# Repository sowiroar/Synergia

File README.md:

# Céfiro
Céfiro is an air quality monitoring project that integrates environmental sensors, embedded systems and machine learning models to predict and analyze atmospheric conditions in the city of Manizales. The project collects data on variables such as temperature, humidity, CO2 concentration and air quality to generate reports and visualizations on the environmental status in real time and over time.

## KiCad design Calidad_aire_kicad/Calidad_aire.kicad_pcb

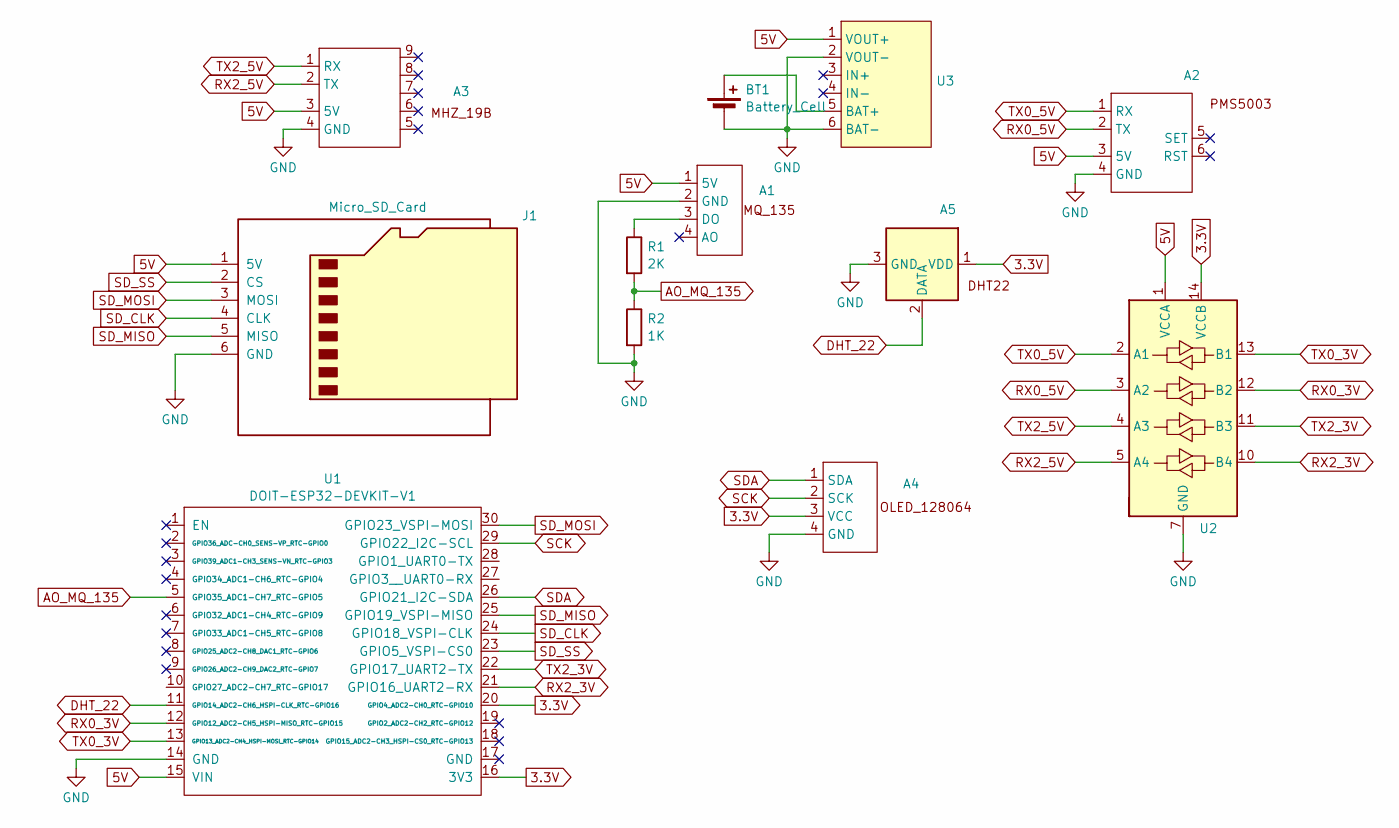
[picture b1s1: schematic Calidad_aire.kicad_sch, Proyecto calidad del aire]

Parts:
A1: MQ_135
A2: TerminalBlock_bornier-4_P5.08mm
A3: MH_Z19B
A4: OLED_128064
A5: DHT22
BT1: Battery_Cell; TerminalBlock_bornier-2_P5.08mm
J1: Micro_SD_Card; microSD
R1: 2K; R_Axial_DIN0414_L11.9mm_D4.5mm_P15.24mm_Horizontal
R2: 1K; R_Axial_DIN0414_L11.9mm_D4.5mm_P15.24mm_Horizontal
U1: DOIT-ESP32-DEVKIT-V1; ESP32_DEVKIT1
U2: conv_niv_log
U3: USB_TP4056

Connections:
3.3V: A4.3 (VCC), A5.1 (VDD), U1.16 (3V3), U1.20 (GPIO4_ADC2-CH0_RTC-GPIO10), U2.14 (VCCB)
5V: A1.1 (5V), A2.3 (5V), A3.3 (5V), J1.1 (5V), U1.15 (VIN), U2.1 (VCCA), U3.1 (VOUT+)
AO_MQ_135: R1.2, R2.1, U1.5 (GPIO35_ADC1-CH7_RTC-GPIO5)
DHT_22: A5.2 (DATA), U1.11 (GPIO14_ADC2-CH6_HSPI-CLK_RTC-GPIO16)
GND: A1.2 (GND), A2.4 (GND), A3.4 (GND), A4.4 (GND), A5.3 (GND), BT1.2 (-), J1.6 (GND), R2.2, U1.14 (GND), U2.7 (GND), U3.2 (VOUT-), U3.6 (BAT-)
unnamed: A1.3 (DO), R1.1
unnamed: BT1.1 (+), U3.5 (BAT+)
RX0_3V: U1.12 (GPIO12_ADC2-CH5_HSPI-MISO_RTC-GPIO15), U2.12 (B2)
RX0_5V: A2.2 (TX), U2.3 (A2)
RX2_3V: U1.21 (GPIO16_UART2-RX), U2.10 (B4)
RX2_5V: A3.2 (TX), U2.5 (A4)
SCK: A4.2 (SCK), U1.29 (GPIO22_I2C-SCL)
SDA: A4.1 (SDA), U1.26 (GPIO21_I2C-SDA)
SD_CLK: J1.4 (CLK), U1.24 (GPIO18_VSPI-CLK)
SD_MISO: J1.5 (MISO), U1.25 (GPIO19_VSPI-MISO)
SD_MOSI: J1.3 (MOSI), U1.30 (GPIO23_VSPI-MOSI)
SD_SS: J1.2 (CS), U1.23 (GPIO5_VSPI-CS0)
TX0_3V: U1.13 (GPIO13_ADC2-CH4_HSPI-MOSI_RTC-GPIO14), U2.13 (B1)
TX0_5V: A2.1 (RX), U2.2 (A1)
TX2_3V: U1.22 (GPIO17_UART2-TX), U2.11 (B3)
TX2_5V: A3.1 (RX), U2.4 (A3)

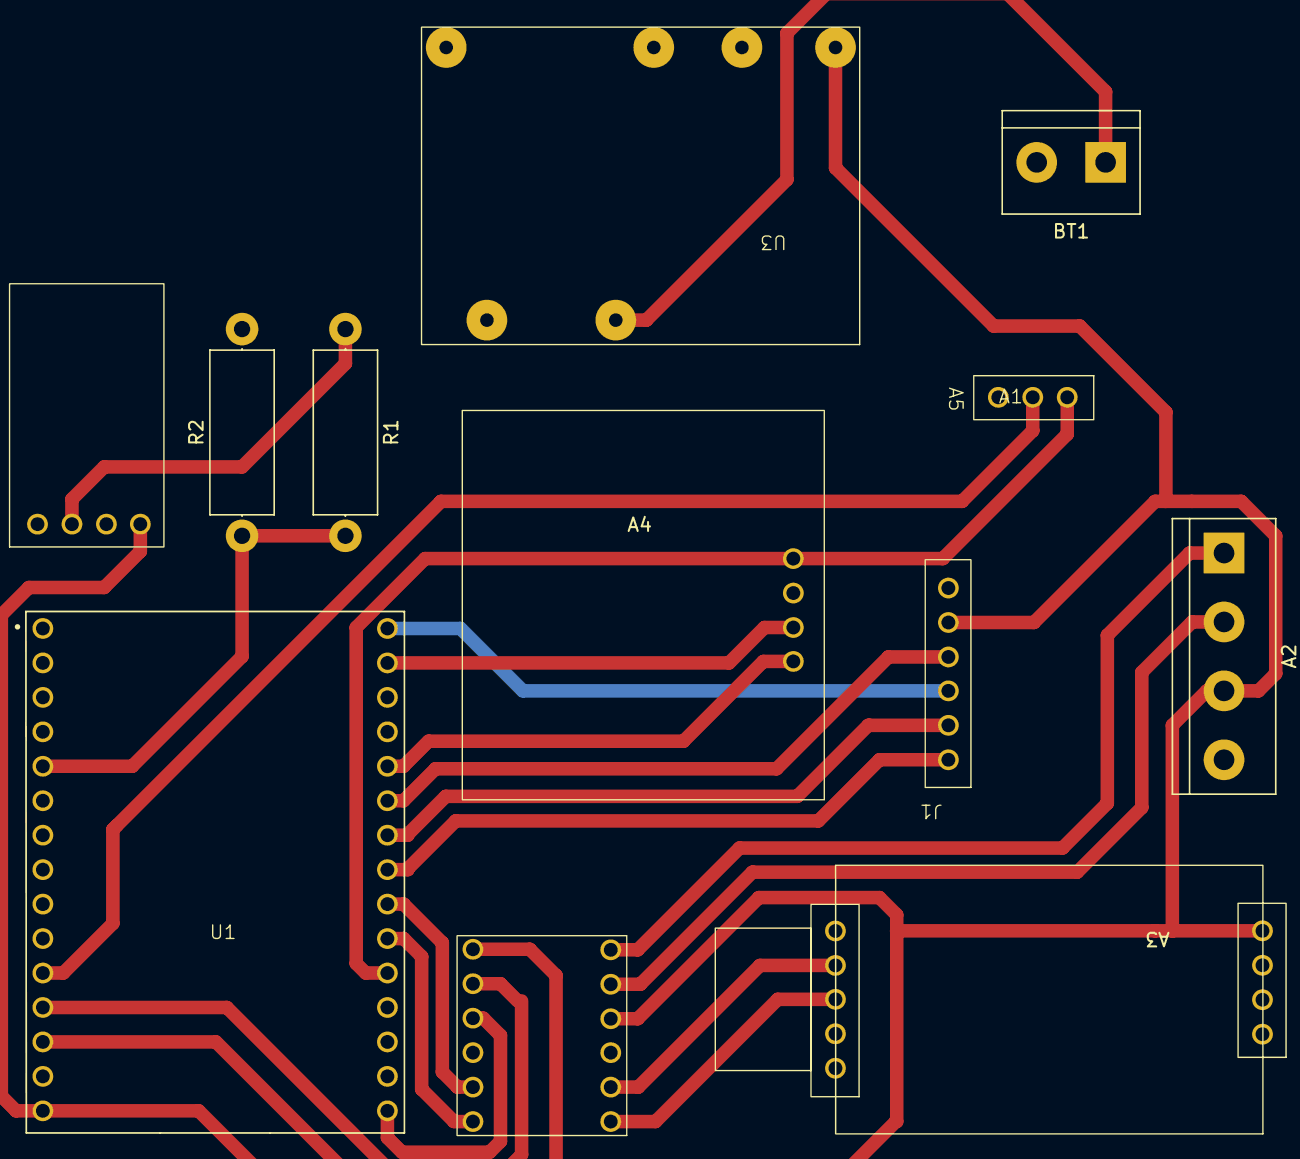
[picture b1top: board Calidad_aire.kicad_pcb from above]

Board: 2 copper layers, 12 parts (0 on the bottom side), 21 nets.

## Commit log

2024-09-13 Update README.md
    Change the name of project
2024-09-13 Create Objetives
    Define which are the objetives of the project
2024-09-13 Create synergia_oled_display.ino
    Proof of oled display
2024-09-13 Upload by local host Ernesto Guevara
2024-09-13 Update README.md
    Change the language
2024-09-13 Delete DHT11 directory
    Its not necesary
2024-09-13 Delete synergia_oled_display.ino
    Move the file to another path
2024-09-13 Files upload by local host Ernesto Guevara
    The folder have the modules for the project
2024-09-13 Create mq7_sensor_reading.ino
    The code for the MQ7
2024-09-13 Create sd_card_initialization.ino
    Test for initializing the microSD
2024-09-13 Create dht22_sensor_reading.ino
    Reads humidity and temperature values using the DHT22 sensor.
2024-09-13 Create sensor_data_logging.ino
    Logs data from DHT22, MQ2, MQ7 sensors to SD card and displays it on OLED.
2024-09-13 Create mz19_sensor.ino
    Reads CO2 and temperature values from the MHZ19 sensor and displays them on the serial monitor
2024-09-13 Create pms5003_sensor.ino
    Reads dust concentration data from the PMS5003 sensor using ESP32 and prints it to the serial monitor
2024-09-13 Add files via upload
    loading files related to kicad
2024-09-13 Update README.md
    Upload the design
2024-09-27 Modification to the schematic design
2024-10-03 Rename cefiro_v1 to cefiro_v1.ino
2024-10-16 Upload the node red code
2024-10-16 Primera versión node-red
2024-10-18 Add files via upload
    Node - red versión 2, prueba inicial con prototipo funcional
2024-10-30 start to PCB design
2024-10-31 Add files via upload
    Código con corrección de guardado de datos en SD
2024-11-01 API for download the dataset
2024-11-03 design of the footprints for the components
2024-11-12 PCB design actualization
2024-11-12 adjustment to the PCB design
2024-12-09 change
